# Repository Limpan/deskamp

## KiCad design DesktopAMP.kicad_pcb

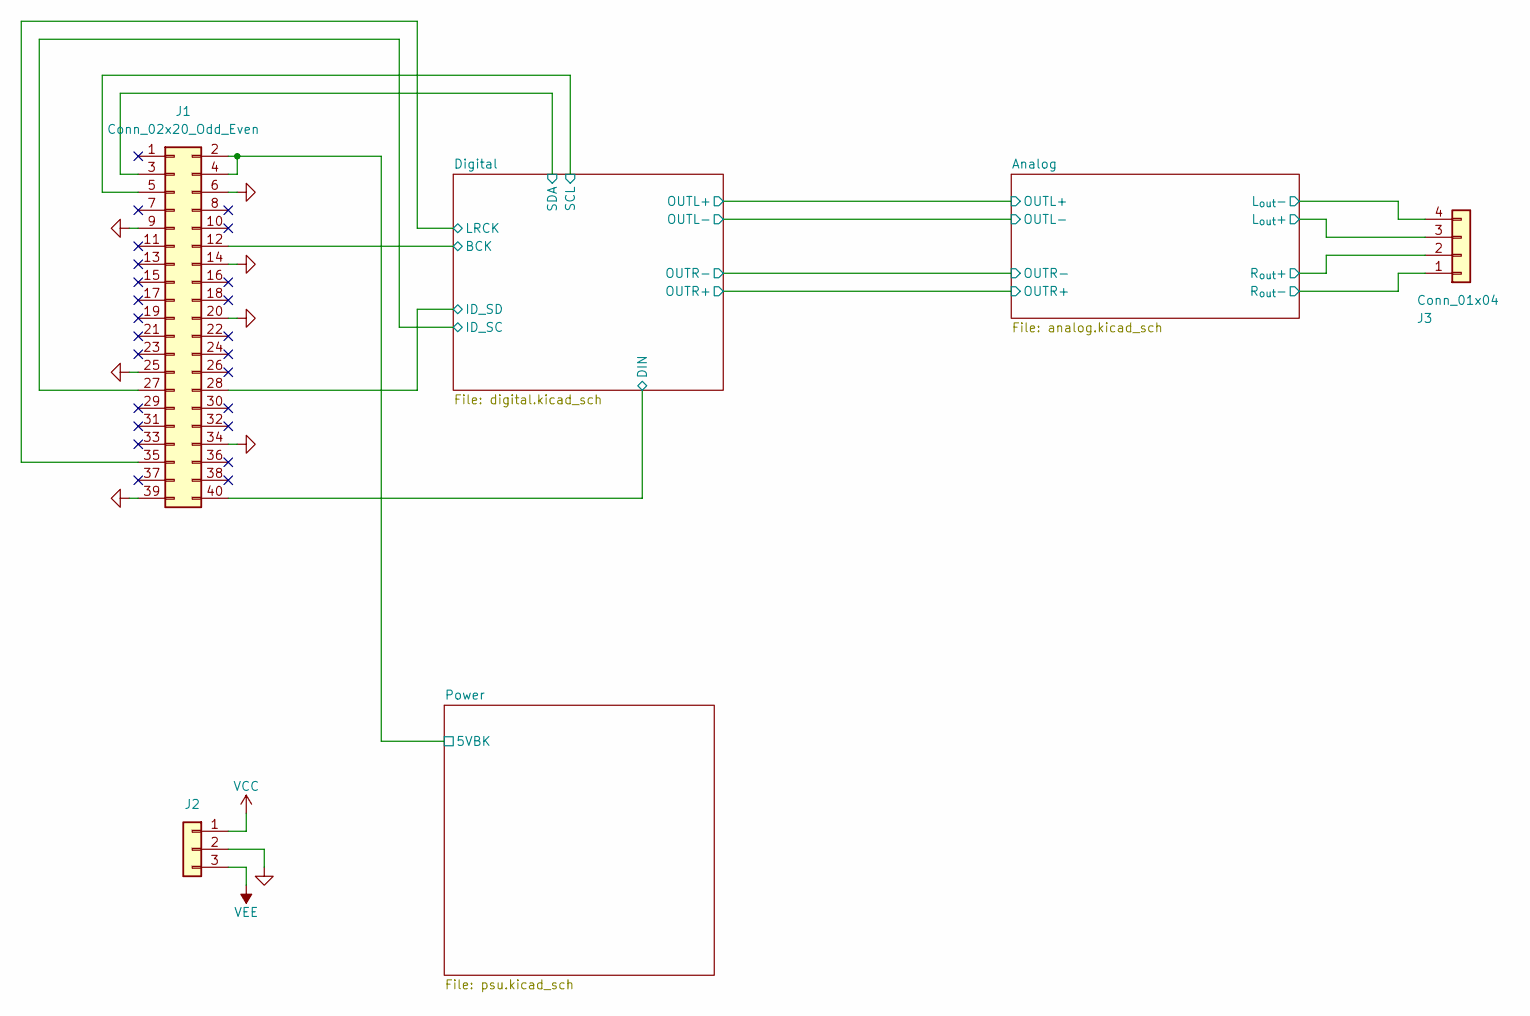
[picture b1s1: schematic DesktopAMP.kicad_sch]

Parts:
J1: Conn_02x20_Odd_Even; RPi_Zero_2W_SMD
J2: Conn_01x03; PhoenixContact_MSTBVA_2,5_3-G_1x03_P5.00mm_Vertical
J3: Conn_01x04; PhoenixContact_MSTBVA_2,5_4-G_1x04_P5.00mm_Vertical

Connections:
/Analog/L_{out}+: J3.3; also elsewhere on the board
/Analog/R_{out}+: J3.2; also elsewhere on the board
/Digital/BCK: J1.12; also elsewhere on the board
/Digital/DIN: J1.40; also elsewhere on the board
/Digital/ID_SC: J1.27; also elsewhere on the board
/Digital/ID_SD: J1.28; also elsewhere on the board
/Digital/LRCK: J1.35; also elsewhere on the board
/Digital/SCL: J1.5; also elsewhere on the board
/Digital/SDA: J1.3; also elsewhere on the board
/Power/5VBK: J1.2, J1.4; also elsewhere on the board
GND: J1.6, J1.9, J1.14, J1.20, J1.25, J1.34, J1.39, J2.2, J3.1, J3.4; also elsewhere on the board
VCC: J2.1; also elsewhere on the board
VEE: J2.3; also elsewhere on the board

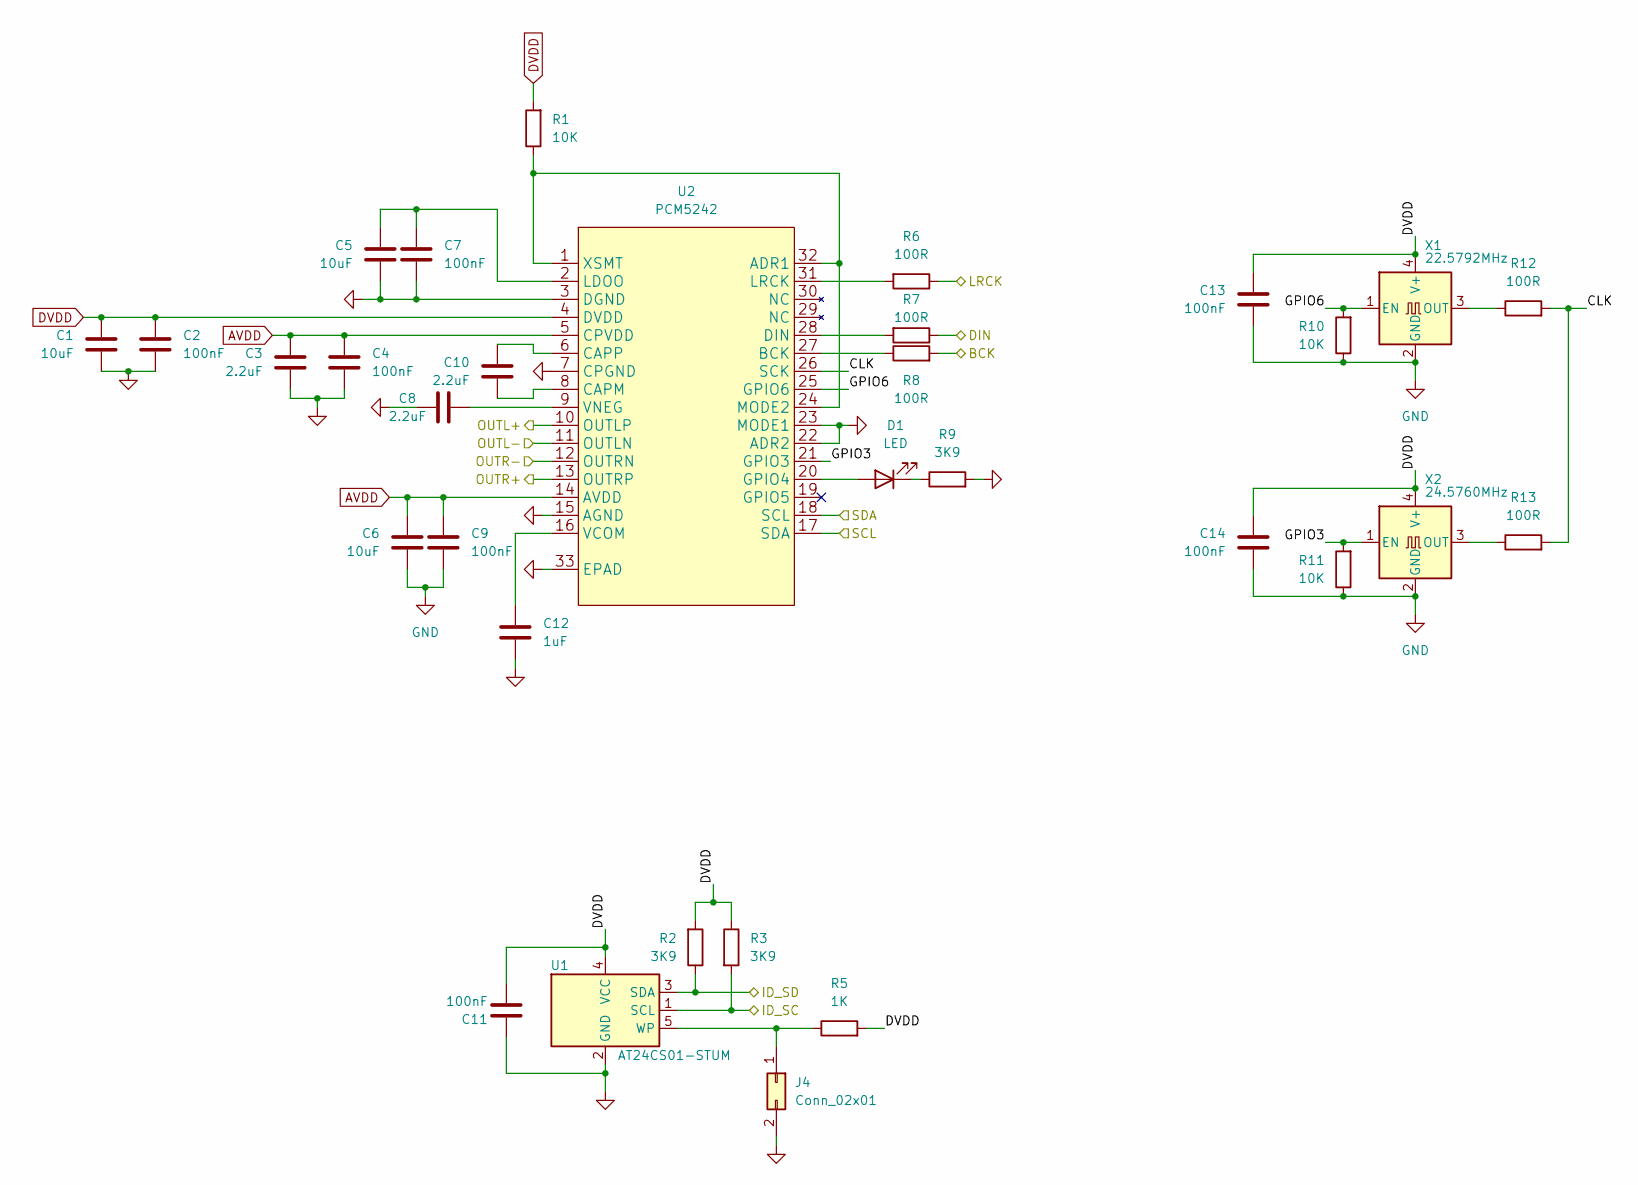
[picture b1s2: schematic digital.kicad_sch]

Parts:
C1, C5, C6: 10uF; C_0805_2012Metric
C2, C4, C7, C9, C11, C13, C14: 100nF; C_0603_1608Metric
C3, C8, C10: 2.2uF; C_0805_2012Metric
C12: 1uF; C_0805_2012Metric
D1: LED; LED_0805_2012Metric
J4: Conn_02x01; PinHeader_1x02_P2.54mm_Vertical
R1, R10, R11: 10K; R_0805_2012Metric
R2, R3, R9: 3K9; R_0805_2012Metric
R5: 1K; R_0805_2012Metric
R6, R7, R8, R12, R13: 100R; R_0805_2012Metric
U1: AT24CS01-STUM; SOT-23-5
U2: PCM5242; Texas_S-PVQFN-N32_EP3.45x3.45mm_ThermalVias
X1: 22.5792MHz; Oscillator_SMD_EuroQuartz_XO53-4Pin_5.0x3.2mm
X2: 24.5760MHz; Oscillator_SMD_EuroQuartz_XO53-4Pin_5.0x3.2mm

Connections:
/Analog/OUTL+: U2.10 (OUTLP); also elsewhere on the board
/Analog/OUTL-: U2.11 (OUTLN); also elsewhere on the board
/Analog/OUTR+: U2.13 (OUTRP); also elsewhere on the board
/Analog/OUTR-: U2.12 (OUTRN); also elsewhere on the board
/Digital/BCK: R8.2; also elsewhere on the board
/Digital/CLK: R12.2, R13.2, U2.26 (SCK)
/Digital/DIN: R7.1; also elsewhere on the board
/Digital/GPIO3: R11.2, U2.21 (GPIO3), X2.1 (EN)
/Digital/GPIO6: R10.2, U2.25 (GPIO6), X1.1 (EN)
/Digital/ID_SC: R3.2, U1.1 (SCL); also elsewhere on the board
/Digital/ID_SD: R2.1, U1.3 (SDA); also elsewhere on the board
/Digital/LRCK: R6.1; also elsewhere on the board
/Digital/SCL: U2.17 (SDA); also elsewhere on the board
/Digital/SDA: U2.18 (SCL); also elsewhere on the board
AVDD: C3.1, C4.1, C6.1, C9.1, U2.5 (CPVDD), U2.14 (AVDD); also elsewhere on the board
DVDD: C1.1, C2.1, C11.2, C13.2, C14.2, R1.2, R2.2, R3.1, R5.2, U1.4 (VCC), U2.4 (DVDD), X1.4 (V+), X2.4 (V+); also elsewhere on the board
GND: C1.2, C2.2, C3.2, C4.2, C5.2, C6.2, C7.2, C8.1, C9.2, C11.1, C12.2, C13.1, C14.1, J4.2, R9.2, R10.1, R11.1, U1.2 (GND), U2.3 (DGND), U2.7 (CPGND), U2.15 (AGND), U2.22 (ADR2), U2.23 (MODE1), U2.33 (EPAD), X1.2 (GND), X2.2 (GND); also elsewhere on the board
unnamed: C5.1, C7.1, U2.2 (LDOO)
unnamed: C8.2, U2.9 (VNEG)
unnamed: C10.1, U2.6 (CAPP)
unnamed: C10.2, U2.8 (CAPM)
unnamed: C12.1, U2.16 (VCOM)
unnamed: D1.1 (K), R9.1
unnamed: D1.2 (A), U2.20 (GPIO4)
unnamed: J4.1, R5.1, U1.5 (WP)
unnamed: R1.1, U2.1 (XSMT), U2.24 (MODE2), U2.32 (ADR1)
unnamed: R6.2, U2.31 (LRCK)
unnamed: R7.2, U2.28 (DIN)
unnamed: R8.1, U2.27 (BCK)
unnamed: R12.1, X1.3 (OUT)
unnamed: R13.1, X2.3 (OUT)

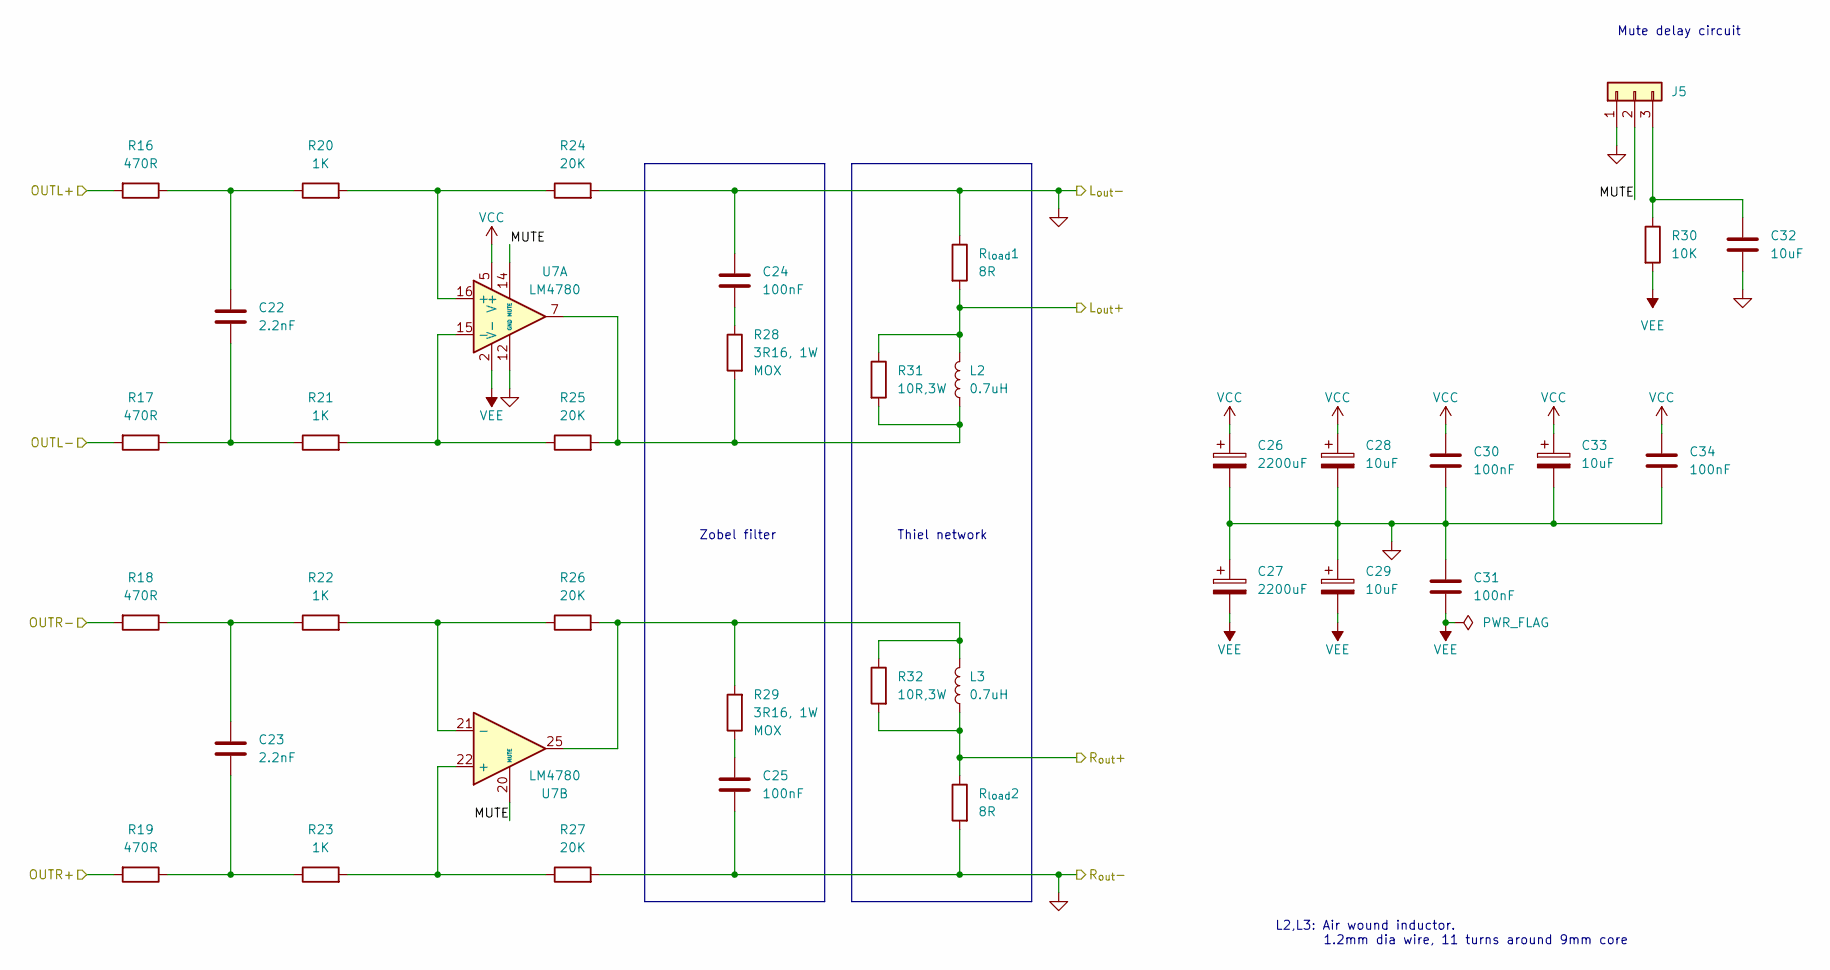
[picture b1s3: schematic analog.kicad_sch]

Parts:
C22, C23: 2.2nF; C_0805_2012Metric
C24, C25, C30, C31, C34: 100nF; C_Rect_L7.2mm_W2.5mm_P5.00mm_FKS2_FKP2_MKS2_MKP2
C26, C27: 2200uF; CP_Radial_D18.0mm_P7.50mm
C28, C29, C33: 10uF; CP_Radial_D6.3mm_P2.50mm
C32: 10uF; C_0805_2012Metric
J5: Conn_01x03; PinHeader_1x03_P2.54mm_Vertical
L2, L3: 0.7uH; L_Axial_L13.25_D11.4_P13.25_Horizontal
R16, R17, R18, R19: 470R; R_0805_2012Metric
R20, R23: 1K; R_0805_2012Metric
R21, R22: 1K; R_Axial_DIN0207_L6.3mm_D2.5mm_P7.62mm_Horizontal
R24, R25, R26, R27: 20K; R_0805_2012Metric
R28, R29: 3R16, 1W; R_Axial_DIN0309_L9.0mm_D3.2mm_P12.70mm_Horizontal
R30: 10K; R_0805_2012Metric
R31, R32: 10R,3W; R_Axial_DIN0617_L17.0mm_D6.0mm_P20.32mm_Horizontal
R_{load}1, R_{load}2: 8R
U7: LM4780; TO-220-27

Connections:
/Analog/L_{out}+: L2.2, R31.1, R_{load}1.2; also elsewhere on the board
/Analog/MUTE: J5.2, U7.14 (MUTE), U7.20 (MUTE)
/Analog/OUTL+: R16.2; also elsewhere on the board
/Analog/OUTL-: R17.2; also elsewhere on the board
/Analog/OUTR+: R19.2; also elsewhere on the board
/Analog/OUTR-: R18.2; also elsewhere on the board
/Analog/R_{out}+: L3.1, R32.2, R_{load}2.1; also elsewhere on the board
GND: C24.1, C25.2, C26.2, C27.1, C28.2, C29.1, C30.2, C31.2, C32.2, C33.2, C34.2, J5.1, R24.2, R27.2, R_{load}1.1, R_{load}2.2, U7.12 (GND), U7.19 (GND); also elsewhere on the board
unnamed: C22.1, R17.1, R21.1
unnamed: C22.2, R16.1, R20.1
unnamed: C23.1, R19.1, R23.1
unnamed: C23.2, R18.1, R22.1
unnamed: C24.2, R28.1
unnamed: C25.1, R29.1
unnamed: C32.1, J5.3, R30.1
unnamed: L2.1, R25.2, R28.2, R31.2, U7.7
unnamed: L3.2, R26.2, R29.2, R32.1, U7.25
unnamed: R20.2, R24.1, U7.16 (+)
unnamed: R21.2, R25.1, U7.15 (-)
unnamed: R22.2, R26.1, U7.21 (-)
unnamed: R23.2, R27.1, U7.22 (+)
VCC: C26.1, C28.1, C30.1, C33.1, C34.1, U7.5 (V+), U7.8 (V+), U7.9 (V+), U7.17 (V+), U7.27 (V+); also elsewhere on the board
VEE: C27.2, C29.2, C31.1, R30.2, U7.2 (V-), U7.4 (V-), U7.10 (V-), U7.11 (V-), U7.18 (V-); also elsewhere on the board

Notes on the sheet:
L2,L3: Air wound inductor. 1.2mm dia wire, 11 turns around 9mm core
Zobel filter
Mute delay circuit
Thiel network

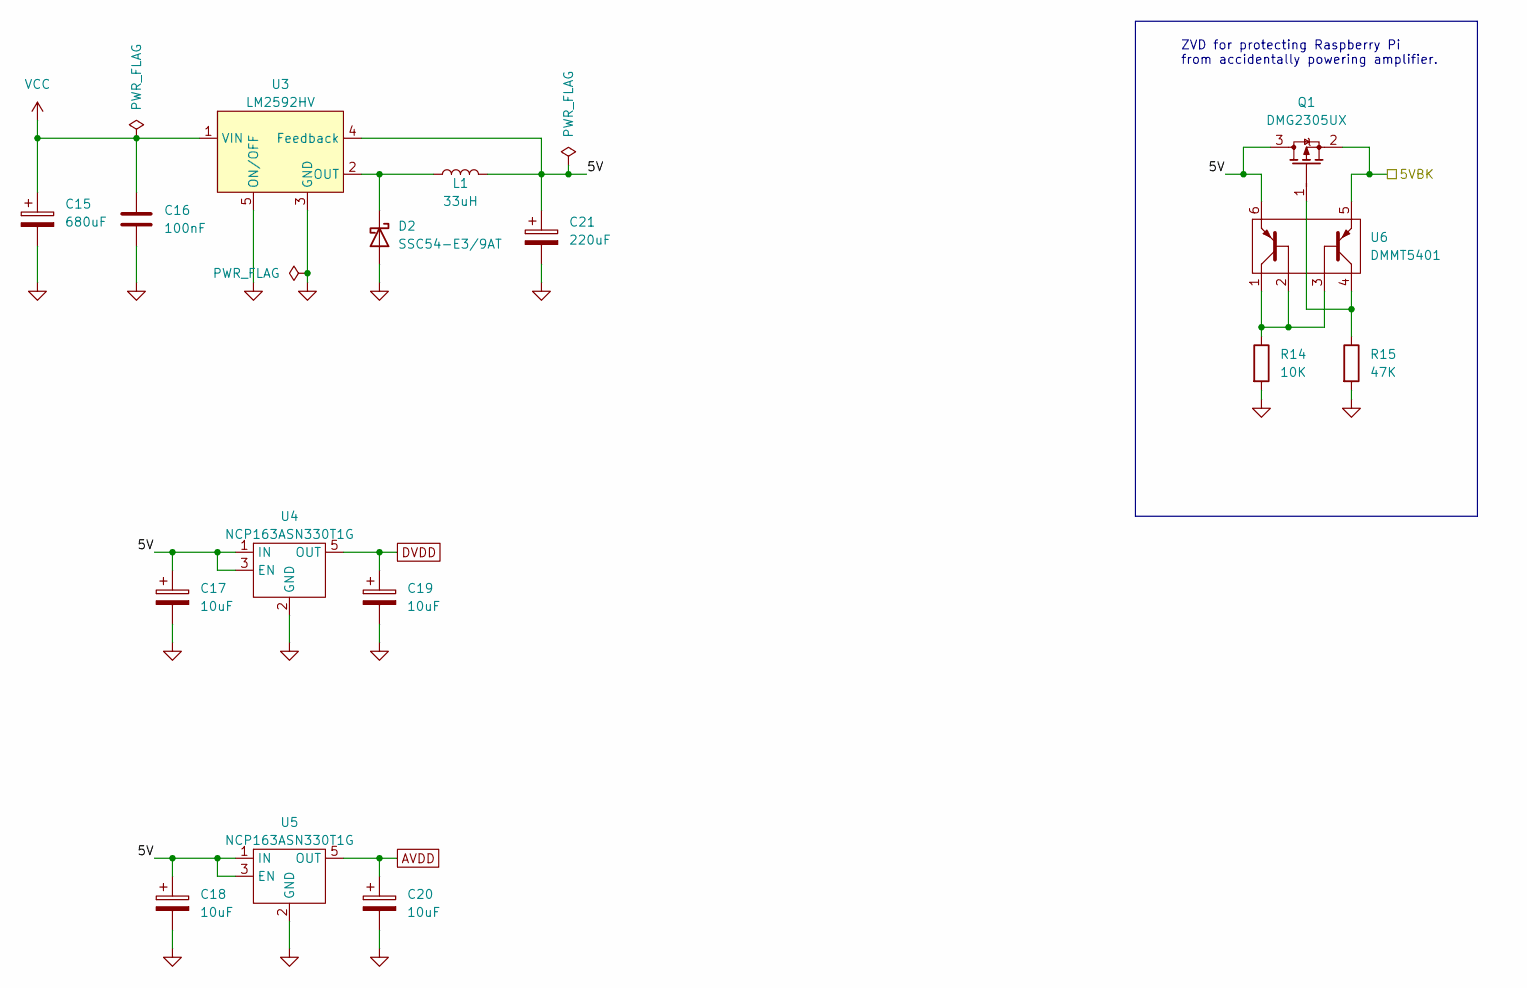
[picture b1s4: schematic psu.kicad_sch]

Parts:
C15: 680uF; CP_Radial_D10.0mm_P3.50mm
C16: 100nF; C_0603_1608Metric
C17, C18, C19, C20: 10uF; C_0805_2012Metric
C21: 220uF; CP_Radial_D8.0mm_P3.50mm
D2: SSC54-E3/9AT; D_SMC
L1: 33uH; L_Bourns_SRR1260
Q1: DMG2305UX; SOT-23
R14: 10K; R_0805_2012Metric
R15: 47K; R_0805_2012Metric
U3: LM2592HV; TO-263-5_TabPin3
U4, U5: NCP163ASN330T1G; SOT-23-5
U6: DMMT5401; SOT-23-6

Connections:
/Power/5V: C17.1, C18.1, C21.1, L1.2, Q1.3, U3.4 (Feedback), U4.1 (IN), U4.3 (EN), U5.1 (IN), U5.3 (EN), U6.6
/Power/5VBK: Q1.2, U6.5; also elsewhere on the board
AVDD: C20.1, U5.5 (OUT); also elsewhere on the board
DVDD: C19.1, U4.5 (OUT); also elsewhere on the board
GND: C15.2, C16.2, C17.2, C18.2, C19.2, C20.2, C21.2, D2.2 (A), R14.2, R15.2, U3.3 (GND), U3.5 (ON/OFF), U4.2 (GND), U4.4 (NC), U5.2 (GND), U5.4 (NC); also elsewhere on the board
unnamed: D2.1 (K), L1.1, U3.2 (OUT)
unnamed: Q1.1, R15.1, U6.4
unnamed: R14.1, U6.1, U6.2, U6.3
VCC: C15.1, C16.1, U3.1 (VIN); also elsewhere on the board

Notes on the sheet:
ZVD for protecting Raspberry Pi from accidentally powering amplifier.

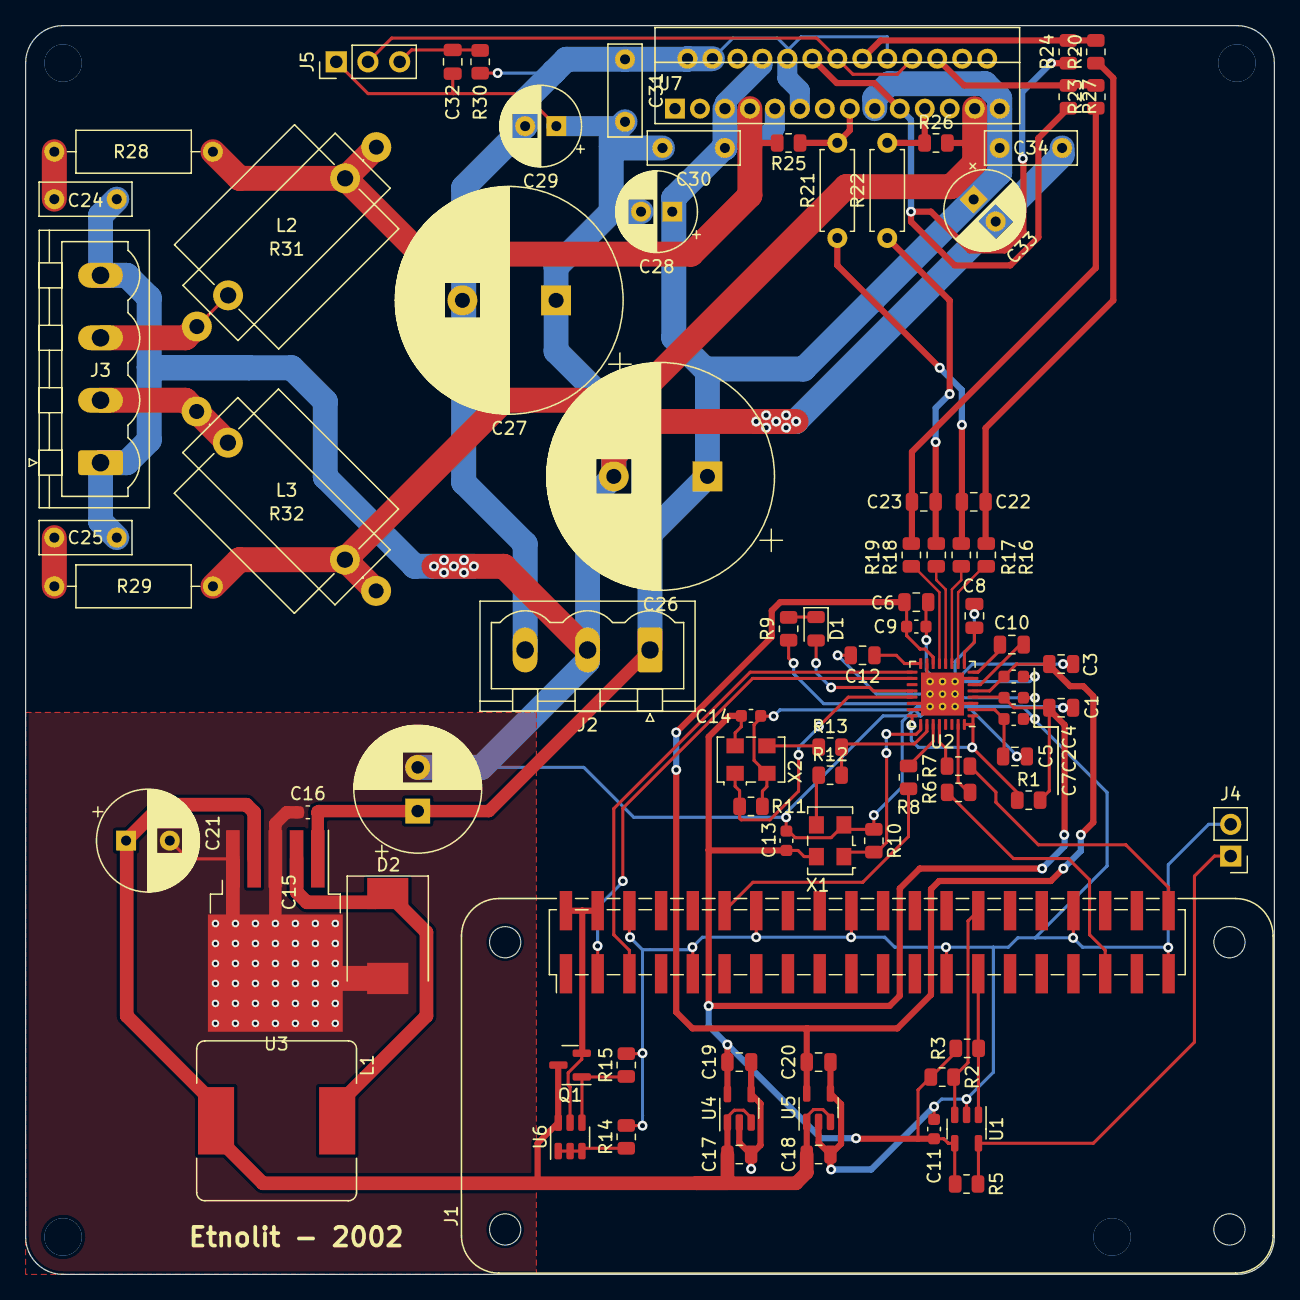
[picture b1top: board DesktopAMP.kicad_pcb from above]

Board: 2 copper layers, 100.0 x 100.0 mm, 85 parts (0 on the bottom side), 54 nets.

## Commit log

2022-02-06 Project setup.
2022-02-07 Added LM4780.
2022-02-07 Added footprints to all components.
2022-02-08 Footprints for all components.
2022-02-08 Worked on placement and footprints.
2022-02-09 Begun splitting schematic into multiple sheets.
